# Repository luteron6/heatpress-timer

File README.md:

# heatpress-timer
The repo for my heat press timer. I created this to solve a problem with my heat press. A heat press basically has a hot metal plate that moves up and down, used to transfer vinyl, DTF transfers, and other 'transfers' to a t-shirt or other garment. The problem is that the timer must be manually stopped and started, making the process inefficient. This project seeks to automate the timer starting and stopping process by detecting when the metal plate is lowered. <br>
It all revolves around this limit switch:
<br><br><br>
When this limit switch closes, it triggers the timer:
<br><br><br>
The piezo is used to alert the user when the timer runs out of time. The plus and minus buttons allow the user to change the ammount of time the timer counts down from.
# BOM
| **Item**                | **QTY Needed** | **QTY Purchased** | **Price** | **Description**                      | **Link**                                                                                                                                                                                                                                                                                                                                                            |
|-------------------------|----------------|-------------------|-----------|--------------------------------------|---------------------------------------------------------------------------------------------------------------------------------------------------------------------------------------------------------------------------------------------------------------------------------------------------------------------------------------------------------------------|
| XIAO ESP32 C6           | 1              | 1                 | $9.84     | The brain!                           | [Link](https://www.aliexpress.us/item/3256807240718259.html?spm=a2g0o.cart.0.0.2c8a38daAsrGCE&mp=1&pdp_npi=5%40dis%21USD%21USD%2010.04%21USD%200.99%21%21USD%200.99%21%21%21%402101d9ee17486551522947928ebc0c%2112000040716079484%21ct%21US%216247076363%21%211%210&pdp_ext_f=%7B%22cart2PdpParams%22%3A%7B%22pdpBusinessMode%22%3A%22retail%22%7D%7D&gatewayAdapt=glo2usa) |
| 2"" LCD Screen          | 1              | 1                 | $8.21     | Countdown display                    | [Link](https://www.aliexpress.us/item/3256808536058388.html?spm=a2g0o.cart.0.0.2c8a38daAsrGCE&mp=1&pdp_npi=5%40dis%21USD%21USD%2011.90%21USD%208.21%21%21USD%208.21%21%21%21%402101d9ee17486551522947928ebc0c%2112000046393978386%21ct%21US%216247076363%21%211%210&gatewayAdapt=glo2usa)|
| Vertical Limit Switches | 10             | 10                | $1.87     | Coundown reset trigger               | [Link](https://www.aliexpress.us/item/3256805965729300.html?spm=a2g0o.cart.0.0.2c8a38daAsrGCE&mp=1&pdp_npi=5%40dis%21USD%21USD%201.99%21USD%201.87%21%21USD%201.87%21%21%21%402101d9ee17486552537122050ebc0c%2112000035998743801%21ct%21US%216247076363%21%211%210&gatewayAdapt=glo2usa)|
| Buzzer                  | 1              | 10                | $2.17     | Alarm                                | [Link](https://www.aliexpress.us/item/3256802480381355.html?spm=a2g0o.cart.0.0.2c8a38daAsrGCE&mp=1&pdp_npi=5%40dis%21USD%21USD%202.37%21USD%202.37%21%21USD%202.37%21%21%21%402101d9ee17486552537122050ebc0c%2112000042917979571%21ct%21US%216247076363%21%211%210&gatewayAdapt=glo2usa)|
| Momentary Buttons       | 2              | 6                 | $1.98     | Buttons to change the countdown time | [Link](https://www.aliexpress.us/item/3256804444014370.html)|
| Solder                  | 1              | 1                 | $10.99    | Ran out of solder                    | [Link](https://pyrodrone.com/products/tbs-solder-spool-100g)|
| Threaded Inserts        | 4              | 400               | $15.98    | Hardware for case                    | [Link](https://www.amazon.com/Ktehloy-Threaded-Assortment-Printing-Components/dp/B0CLKDPN65/ref=sr_1_1_sspa?sr=8-1-spons&sp_csd=d2lkZ2V0TmFtZT1zcF9hdGY)|
| PCB                     | 1              | 5                 | $13.55    | Price for PCB and shipping at JLCPCB |                  |
|                         |                |                   |           |                                      |                                                                                                                                                                                                                                                                                                                                                                     |
| Sales Tax               |                |                   | $3.96     |                                      |                                                                                                                                                                                                                                                                                                                                                                     |
| Shipping                |                |                   | $11.12    | Aliexpress Shipping                  |                                                                                                                                                                                                                                                                                                                                                                     |
| Shipping                |                |                   | $9.77     | Pyrodrone Shipping                   |                                                                                                                                                                                                                                                                                                                                                                     |
|                         |                |                   |           |                                      |                                                                                                                                                                                                                                                                                                                                                                     |
| TOTAL                   |                |                   | $89.44    |                                      |                                                                                                                                                                                                                                                                                                                                                                     |

There's three main parts:
### The CAD
The case! Three parts, the top/bottom of the case, and the vertical switch mount. The /CAD folder has all the parts as a STL, and everything in the STEP file. Meant to be 3D printed.

### The PCB
It connects all the electronics! It's meant to be bolted to the back of the screen. Both the KiCAD source files and the gerber files are in there.

### The Code
I designed the code to run on [CircuitPython](https://circuitpython.org/board/seeed_xiao_esp32c6/). Still a work in progress, but essentially it changes the time with the buttons (+ and -), it resets the timer when the limit switch is triggered, and beeps when the timer is at 0. The last known time is stored in the file settings.txt so that it persists across reboots. Drop/upload all the files in /Code into the REPL once CircuitPython is installed on the ESP.

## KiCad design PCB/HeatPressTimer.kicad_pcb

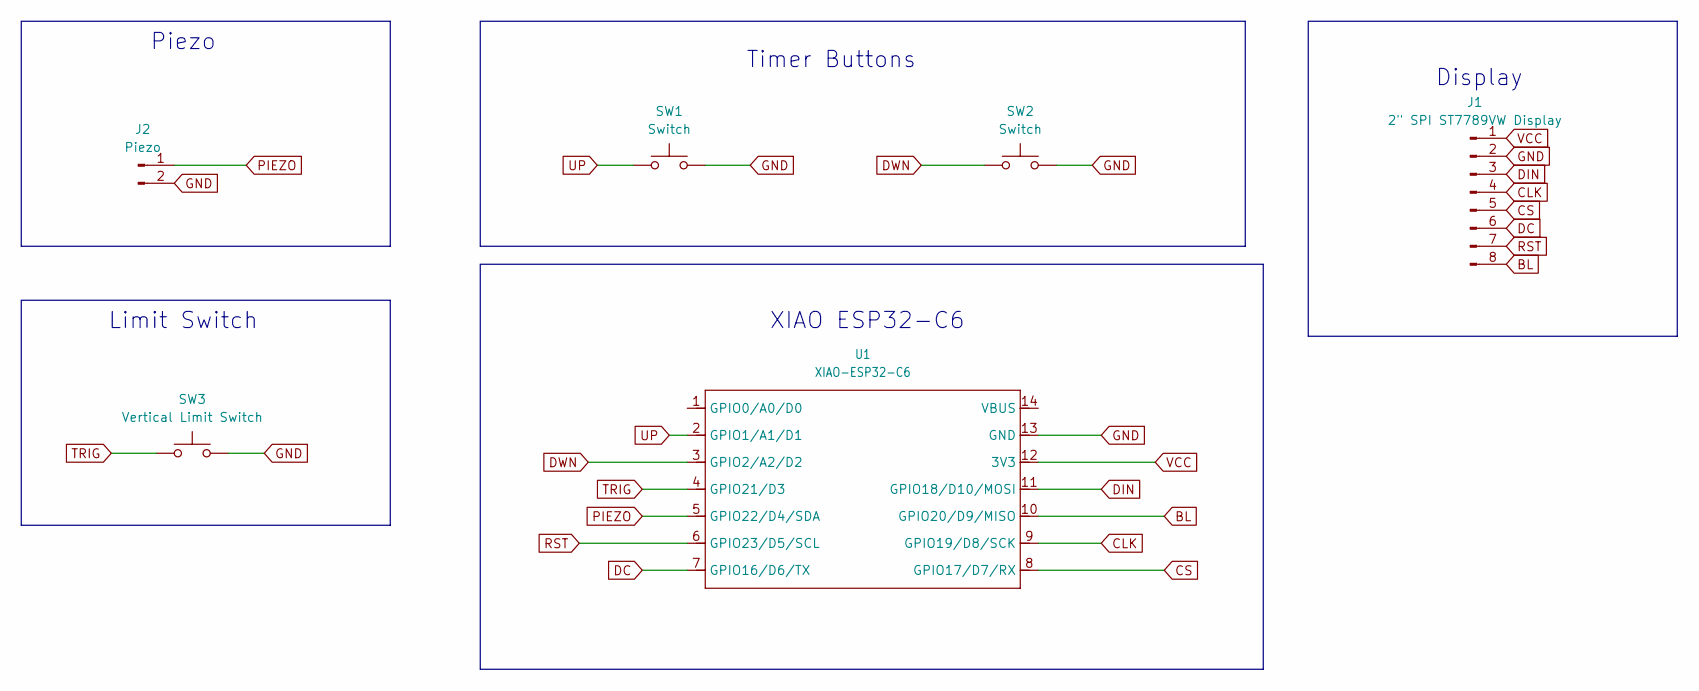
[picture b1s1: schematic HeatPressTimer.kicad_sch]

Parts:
J1: 2" SPI ST7789VW Display; 8-pin pads
J2: Piezo; Buzzer
SW1, SW2: Switch; 2-pin pads
SW3: Vertical Limit Switch; Vertical Switch
U1: XIAO-ESP32-C6; XIAO-ESP32C6-DIP

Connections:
BL: J1.8, U1.10 (GPIO20/D9/MISO)
CLK: J1.4, U1.9 (GPIO19/D8/SCK)
CS: J1.5, U1.8 (GPIO17/D7/RX)
DC: J1.6, U1.7 (GPIO16/D6/TX)
DIN: J1.3, U1.11 (GPIO18/D10/MOSI)
DWN: SW2.1, U1.3 (GPIO2/A2/D2)
GND: J1.2, J2.2, SW1.2, SW2.2, SW3.2, U1.13 (GND)
PIEZO: J2.1, U1.5 (GPIO22/D4/SDA)
RST: J1.7, U1.6 (GPIO23/D5/SCL)
TRIG: SW3.1, U1.4 (GPIO21/D3)
UP: SW1.1, U1.2 (GPIO1/A1/D1)
VCC: J1.1, U1.12 (3V3)

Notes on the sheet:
XIAO ESP32-C6
Piezo
Limit Switch
Timer Buttons
Display

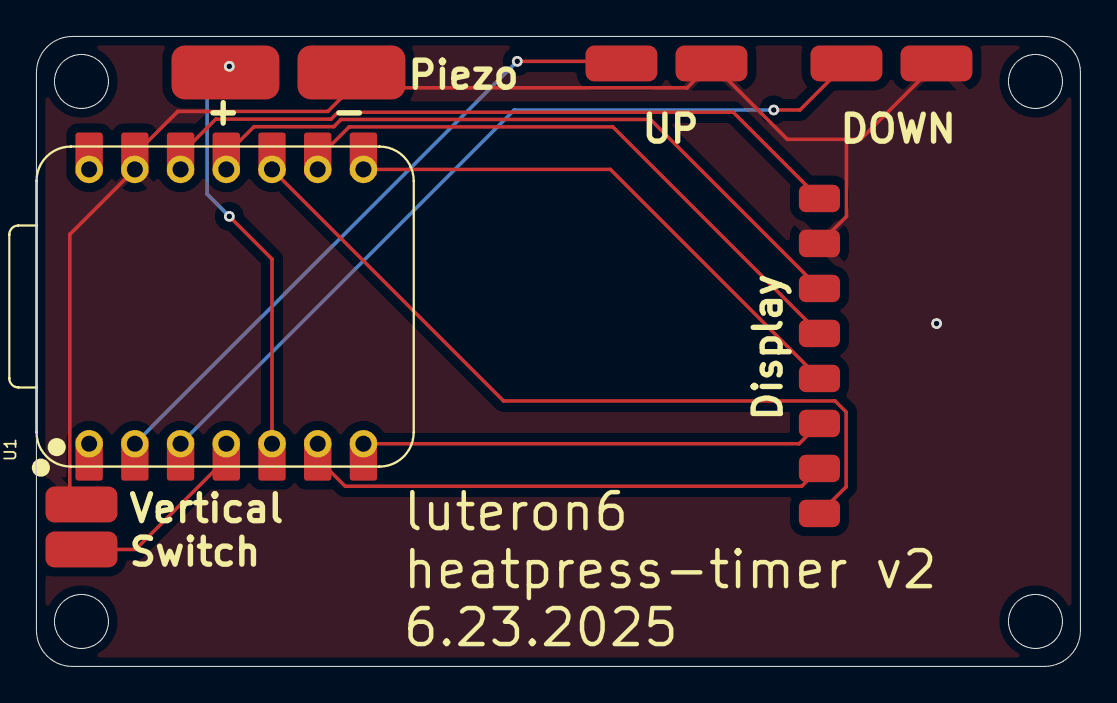
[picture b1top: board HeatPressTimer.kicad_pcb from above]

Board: 2 copper layers, 58.0 x 35.0 mm, 6 parts (0 on the bottom side), 12 nets.

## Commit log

2025-05-20 Create JOURNAL.md and add day 1 log
2025-05-20 Update JOURNAL.md - Day 2!
2025-05-20 some edits to journal.md
2025-05-20 Found cheaper parts!
2025-05-21 fixed line breaks
2025-05-21 Day 3!
2025-05-24 Day 51
2025-05-26 Day 6!
2025-05-31 Added CAD, Code, and PCB files!
2025-05-31 Added source files and BOM
2025-05-31 Added description to BOM
2025-06-07 Added BOM
2025-06-07 added PCB to BOM
2025-06-07 Updated case screenshot
2025-06-07 Updated CAD files
2025-06-22 Day 9!
2025-06-23 new PCB files
2025-06-23 Day 10!
2025-06-24 Added filled zone to PCB
2025-07-02 sketchy working code
2025-07-02 Fixed CAD
    Made base taller, added vertical endstop mount.
2025-07-02 Added working code
    Fixed code, added libraries and fonts
2025-07-02 Day 11!
